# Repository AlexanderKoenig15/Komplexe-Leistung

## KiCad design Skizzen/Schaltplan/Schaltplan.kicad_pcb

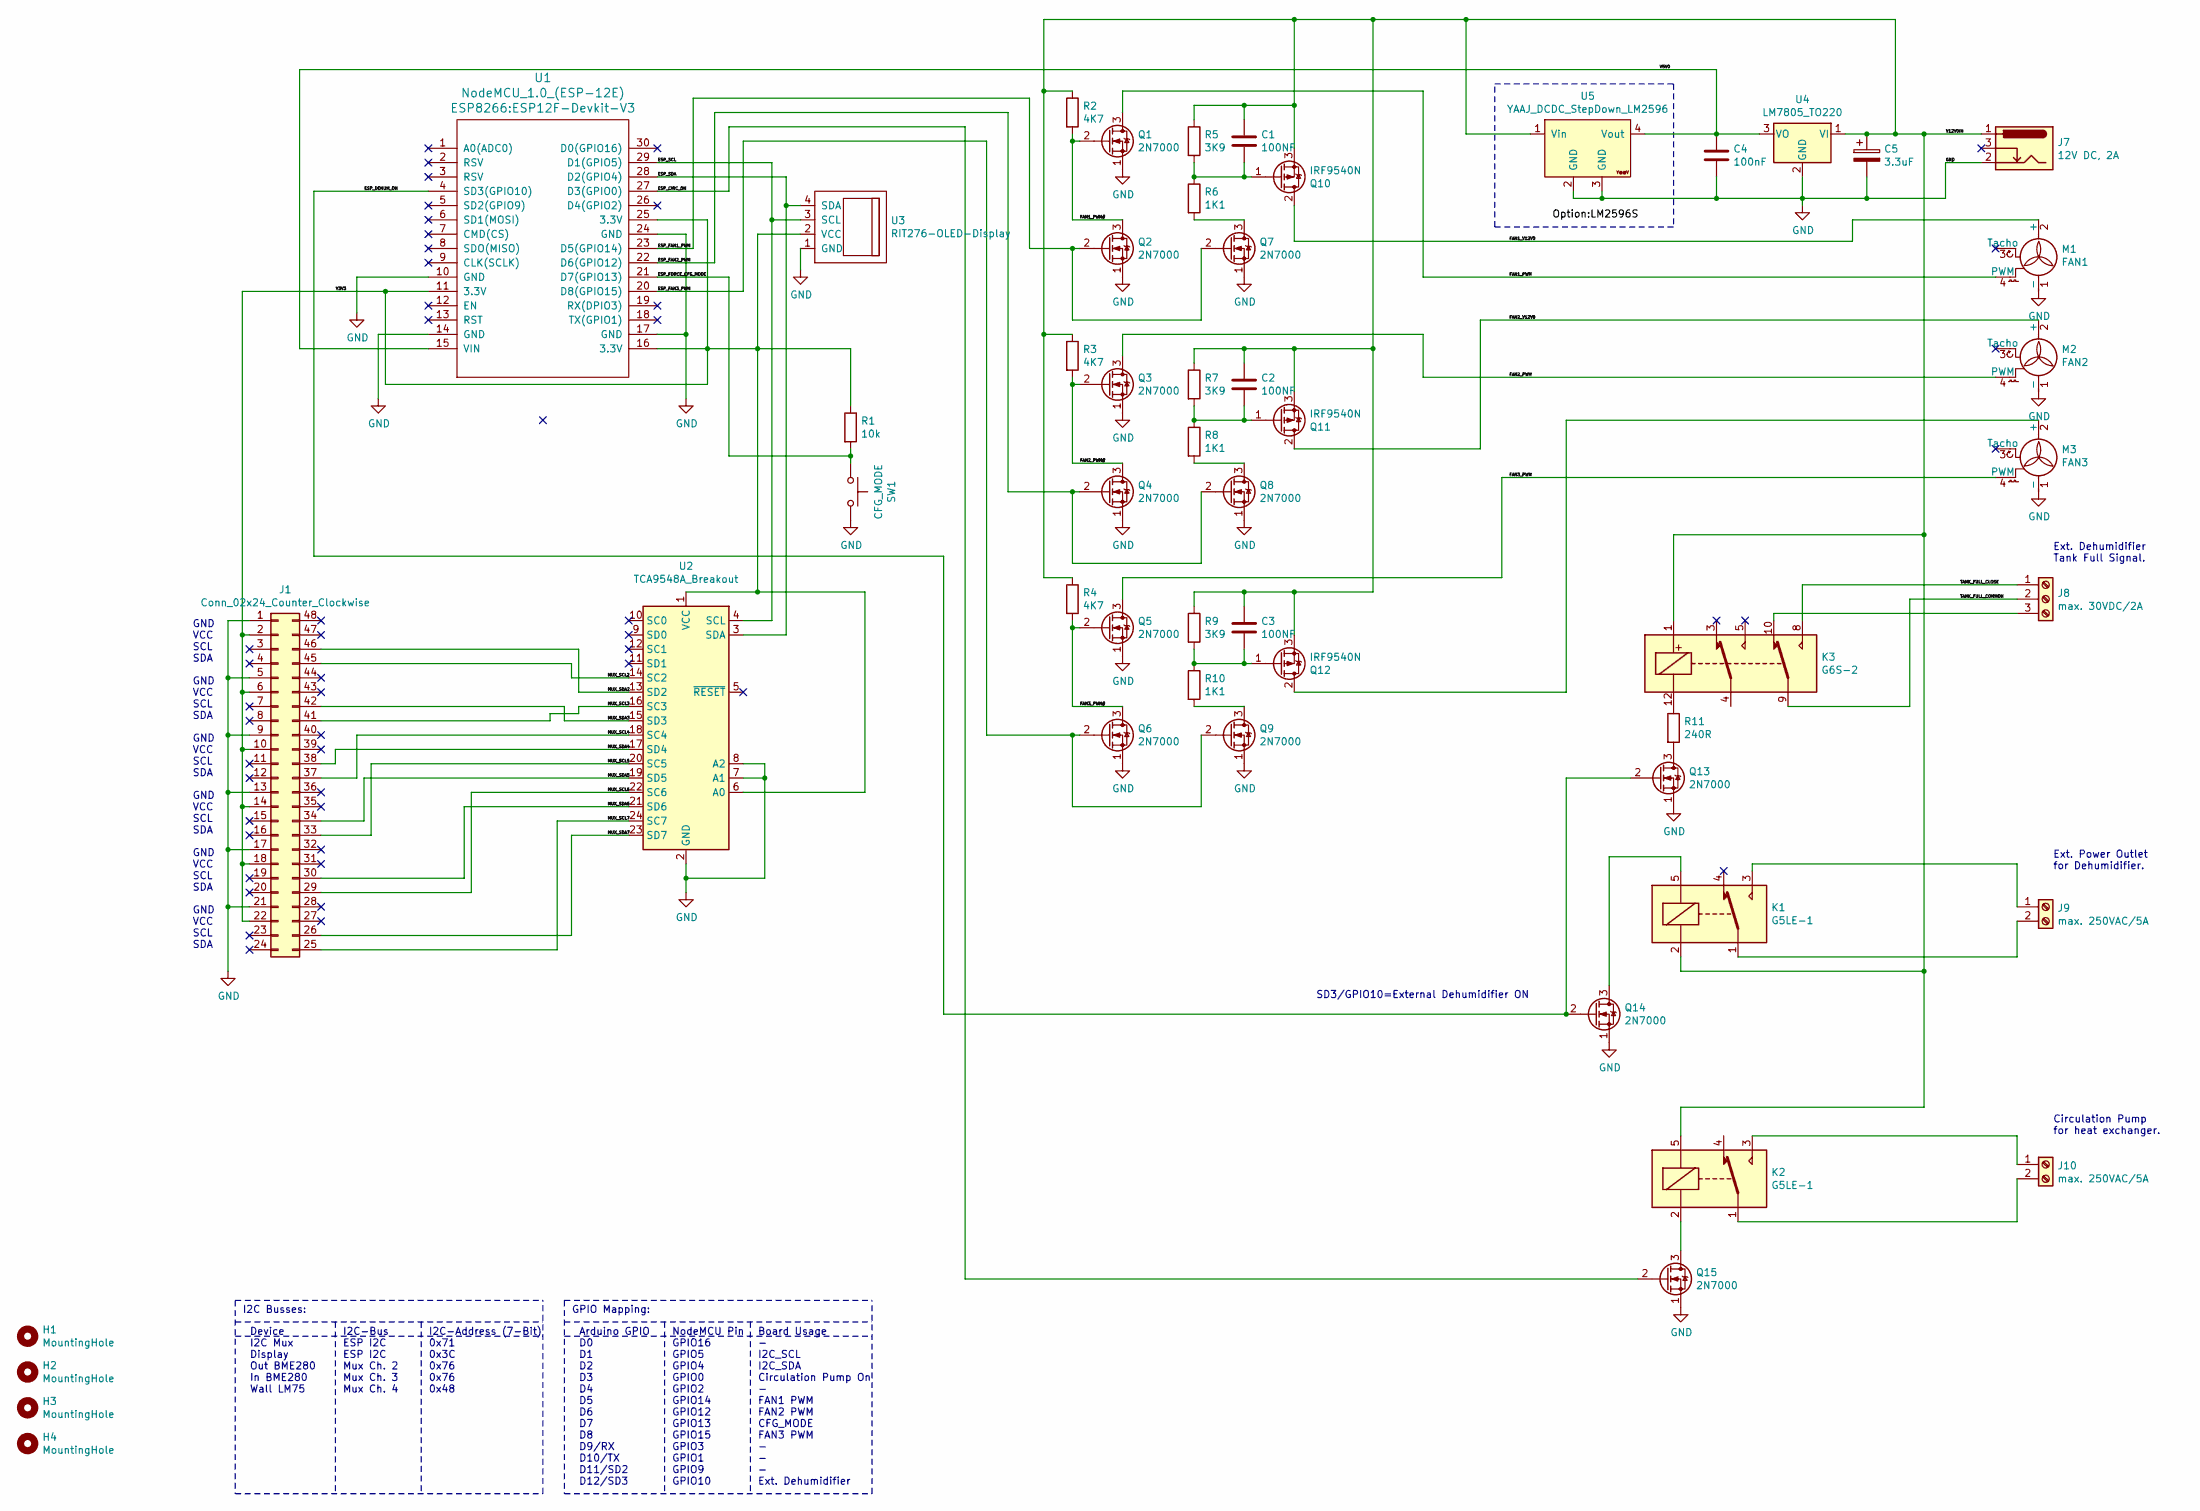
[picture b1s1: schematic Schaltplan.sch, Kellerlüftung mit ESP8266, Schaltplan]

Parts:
C1, C2, C3: 100NF; C_Disc_D4.3mm_W1.9mm_P5.00mm
C4: 100nF; C_Disc_D4.3mm_W1.9mm_P5.00mm
C5: 3.3uF; CP_Radial_Tantal_D4.5mm_P5.00mm
H1, H2, H3, H4: MountingHole; MountingHole_3.2mm_M3
J1: Conn_02x24_Counter_Clockwise; FFKDSH-2,54_24
J7: 12V DC, 2A; PinHeader_1x03_P2.54mm_Vertical
J8: max. 30VDC/2A; TerminalBlock_RND_205-00002_1x03_P5.00mm_Horizontal
J9, J10: max. 250VAC/5A; TerminalBlock_RND_205-00001_1x02_P5.00mm_Horizontal
K1, K2: G5LE-1; Relay_SPDT_Omron-G5LE-1
K3: G6S-2; Relay_DPDT_Omron_G6S-2
M1: FAN1; PinSocket_1x04_P2.54mm_Vertical
M2: FAN2; PinSocket_1x04_P2.54mm_Vertical
M3: FAN3; PinSocket_1x04_P2.54mm_Vertical
Q1, Q2, Q3, Q4, Q5, Q6, Q7, Q8, Q9, Q13, Q14, Q15: 2N7000; TO-92_Inline
Q10, Q11, Q12: IRF9540N; TO-220-3_Vertical
R1: 10k; R_Axial_DIN0204_L3.6mm_D1.6mm_P2.54mm_Vertical
R2, R3, R4: 4K7; R_Axial_DIN0204_L3.6mm_D1.6mm_P2.54mm_Vertical
R5, R7, R9: 3K9; R_Axial_DIN0204_L3.6mm_D1.6mm_P2.54mm_Vertical
R6, R8, R10: 1K1; R_Axial_DIN0204_L3.6mm_D1.6mm_P7.62mm_Horizontal
R11: 240R; R_Axial_DIN0204_L3.6mm_D1.6mm_P2.54mm_Vertical
SW1: CFG_MODE; PinHeader_1x02_P2.54mm_Vertical
U1: NodeMCU_1.0_(ESP-12E); ESP12F-Devkit-V3
U2: TCA9548A_Breakout
U3: RIT276-OLED-Display; SSD1306_128x64_0.96
U4: LM7805_TO220; TO-220-3_Vertical
U5: YAAJ_DCDC_StepDown_LM2596

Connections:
/ESP_CIRC_ON: Q15.2 (G), U1.27 (D3(GPIO0))
/ESP_DEHUM_ON: Q13.2 (G), Q14.2 (G), U1.4 (SD3(GPIO10))
/ESP_FAN1_PWM: Q2.2 (G), Q7.2 (G), U1.23 (D5(GPIO14))
/ESP_FAN2_PWM: Q4.2 (G), Q8.2 (G), U1.22 (D6(GPIO12))
/ESP_FAN3_PWM: Q6.2 (G), Q9.2 (G), U1.20 (D8(GPIO15))
/ESP_FORCE_CFG_MODE: R1.2, SW1.1, U1.21 (D7(GPIO13))
/ESP_SCL: U1.29 (D1(GPIO5)), U2.4 (SCL), U3.3 (SCL)
/ESP_SDA: U1.28 (D2(GPIO4)), U2.3 (SDA), U3.4 (SDA)
/FAN1_PWM: M1.4 (PWM), Q1.3 (D)
/FAN1_PWM#: Q1.2 (G), Q2.3 (D), R2.2
/FAN1_V12V0: M1.2 (+), Q10.2 (D)
/FAN2_PWM: M2.4 (PWM), Q3.3 (D)
/FAN2_PWM#: Q3.2 (G), Q4.3 (D), R3.2
/FAN2_V12V0: M2.2 (+), Q11.2 (D)
/FAN3_PWM: M3.4 (PWM), Q5.3 (D)
/FAN3_PWM#: Q5.2 (G), Q6.3 (D), R4.2
/MUX_SCL2: J1.45, U2.14 (SC2)
/MUX_SCL3: J1.41, U2.16 (SC3)
/MUX_SCL4: J1.37, U2.18 (SC4)
/MUX_SCL5: J1.33, U2.20 (SC5)
/MUX_SCL6: J1.29, U2.22 (SC6)
/MUX_SCL7: J1.25, U2.24 (SC7)
/MUX_SDA2: J1.46, U2.13 (SD2)
/MUX_SDA3: J1.42, U2.15 (SD3)
/MUX_SDA4: J1.38, U2.17 (SD4)
/MUX_SDA5: J1.34, U2.19 (SD5)
/MUX_SDA6: J1.30, U2.21 (SD6)
/MUX_SDA7: J1.26, U2.23 (SD7)
/TANK_FULL_CLOSE: J8.1, K3.8
/TANK_FULL_COMMON: J8.2, K3.9
/V3V3: J1.2, J1.6, J1.10, J1.14, J1.18, J1.22, R1.1, U1.11 (3.3V), U1.16 (3.3V), U1.25 (3.3V), U2.1 (VCC), U2.6 (A0), U3.2 (VCC)
/V5V0: C4.1, U1.15 (VIN), U4.3 (VO), U5.4 (Vout)
/V12V0IN: C1.1, C2.1, C3.1, C5.1, J7.1, K1.2, K2.5, K3.1, Q10.3 (S), Q11.3 (S), Q12.3 (S), R2.1, R3.1, R4.1, R5.1, R7.1, R9.1, U4.1 (VI), U5.1 (Vin)
GND: C4.2, C5.2, J1.1, J1.5, J1.9, J1.13, J1.17, J1.21, J7.2, M1.1 (-), M2.1 (-), M3.1 (-), Q1.1 (S), Q2.1 (S), Q3.1 (S), Q4.1 (S), Q5.1 (S), Q6.1 (S), Q7.1 (S), Q8.1 (S), Q9.1 (S), Q13.1 (S), Q14.1 (S), Q15.1 (S), SW1.2, U1.10 (GND), U1.14 (GND), U1.17 (GND), U1.24 (GND), U2.2 (GND), U2.7 (A1), U2.8 (A2), U3.1 (GND), U4.2 (GND), U5.2 (GND), U5.3 (GND)
unnamed: C1.2, Q10.1 (G), R5.2, R6.1
unnamed: C2.2, Q11.1 (G), R7.2, R8.1
unnamed: C3.2, Q12.1 (G), R9.2, R10.1
unnamed: J8.3, K3.10
unnamed: J9.1, K1.3
unnamed: J9.2, K1.1
unnamed: J10.1, K2.3
unnamed: J10.2, K2.1
unnamed: K1.5, Q14.3 (D)
unnamed: K2.2, Q15.3 (D)
unnamed: K3.12, R11.1
unnamed: M3.2 (+), Q12.2 (D)
unnamed: Q7.3 (D), R6.2
unnamed: Q8.3 (D), R8.2
unnamed: Q9.3 (D), R10.2
unnamed: Q13.3 (D), R11.2

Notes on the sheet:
SD3/GPIO10=External Dehumidifier ON
Ext. Power Outlet for Dehumidifier.
Ext. Dehumidifier Tank Full Signal.
Circulation Pump for heat exchanger.
GPIO Mapping:
Arduino GPIO D0 D1 D2 D3 D4 D5 D6 D7 D8 D9/RX D10/TX D11/SD2 D12/SD3
NodeMCU Pin GPIO16 GPIO5 GPIO4 GPIO0 GPIO2 GPIO14 GPIO12 GPIO13 GPIO15 GPIO3 GPIO1 GPIO9 GPIO10
Board Usage - I2C_SCL I2C_SDA Circulation Pump On - FAN1 PWM FAN2 PWM CFG_MODE FAN3 PWM - - - Ext. Dehumidifier
GND VCC SCL SDA
I2C Busses:
I2C-Bus ESP I2C ESP I2C Mux Ch. 2 Mux Ch. 3 Mux Ch. 4
Device I2C Mux Display Out BME280 In BME280 Wall LM75
I2C-Address (7-Bit) 0x71 0x3C 0x76 0x76 0x48

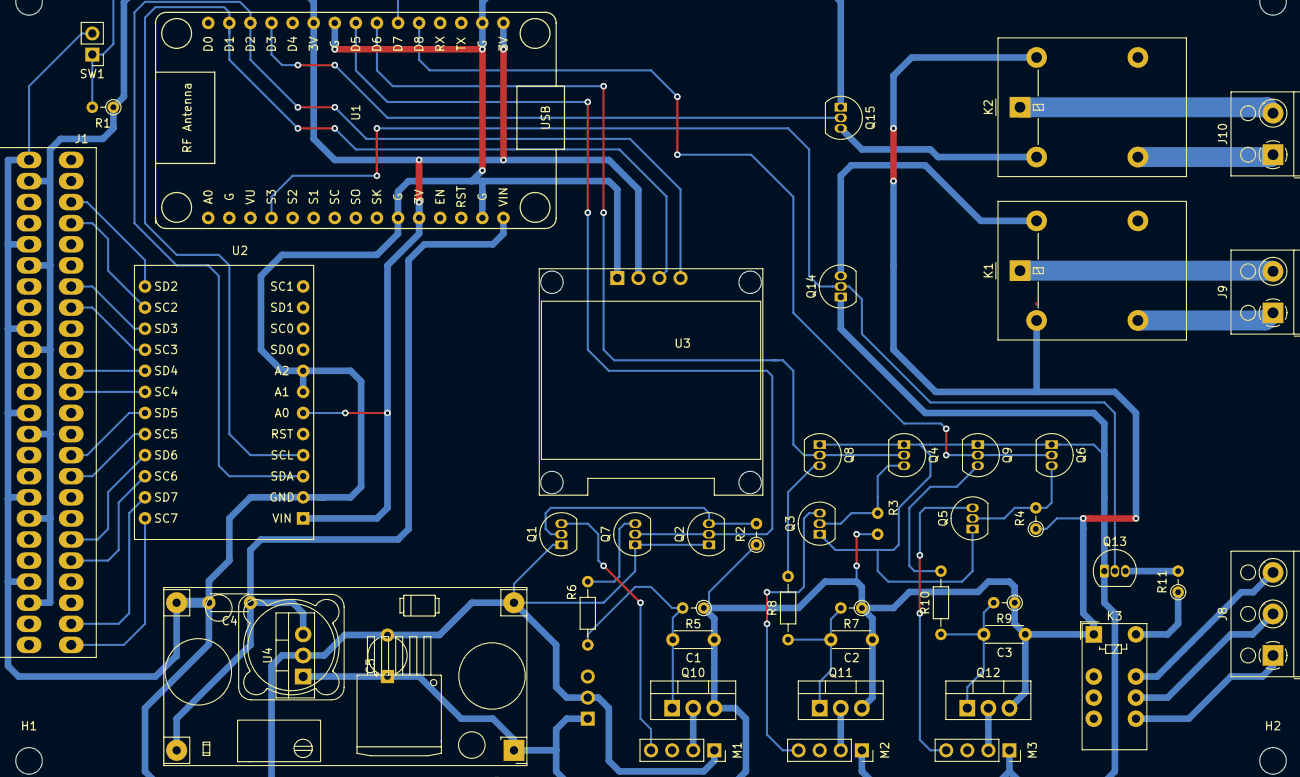
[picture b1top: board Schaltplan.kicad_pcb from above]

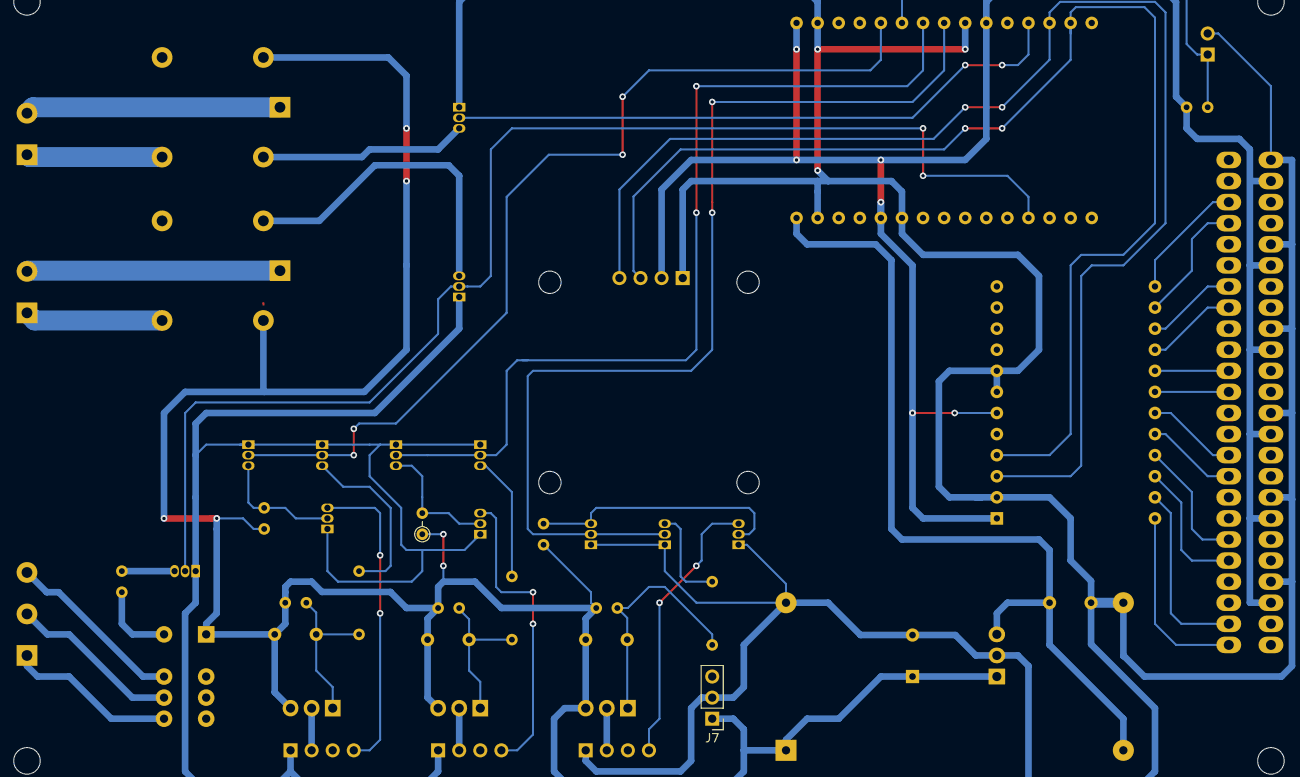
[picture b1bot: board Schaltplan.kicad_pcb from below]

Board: 2 copper layers, 52 parts (2 on the bottom side), 50 nets.

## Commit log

2021-08-01 Anfang
2021-08-30 Woche 1 22.80.2021 - 29.8.2021
2021-09-06 Woche 2 29.09.2021 - 05.09.2021
    -Code fertig
2021-09-13 Woche 3 05.09.2021 - 12.09.2021
2021-09-20 Woche 4 13.09.2021-20.09.2021
2021-09-27 Woche 5 19.09.2021 - 26.09.2021
2021-10-05 Woche 6 26.09.2021 - 01.10.2021
2021-10-11 Woche 7 01.10.2021 - 03.10.2021
2021-10-18 Woche 8 10.10.2021 - 17.10.2021
2021-10-25 Woche 9 17.10.2021 - 24.10.2021
2021-11-02 Woche 10 24.10.2021 - 31.10.2021
2021-11-08 Woche 11 31.10.2021 - 7.11.2021
2021-11-22 Woche 12&13 07.11.2021 -21.11.2021
2021-11-29 Woche 14 21.11.2021 - 28.11.2021
2021-12-06 Woche 15 28.11.2021 - 5.12.2021
2022-01-03 bis Woche 19 5.12.2021 - 02.01.2022
2022-01-10 Woche 20 02.01.2022 - 08.01.2022
2022-01-17 Woche 21 09.01.2022 - 16.01.2022
2022-01-24 Woche 22 16.01.2022 - 23.01.2022
2022-01-31 Woche 23 23.01.2022 - 30.01.2022
2022-02-07 Woche 24 30.01.2022 - 06.01.2022
2023-09-05 Nacharbeit v1
2023-09-23 Nacharbeit v2
2023-10-10 Nacharbeit v3
